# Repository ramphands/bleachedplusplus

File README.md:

# bleached++
slightly expanded and simplified version of the original Bleached PCB design by [andr-ew](https://github.com/andr-ew/bleached)

Bleached++ in operation

Render of the board

PCB layout with dimensions

## BOM
### board:
1x TeensyLC

2x 14-pin pin headers.

9x 10K linear potentiometers

### mounting HW:
4x 10mm M2.5 female-female standoffs - to be used between the board and the top panel

4x 5mm* M2.5 male-female standoffs  - to be used between the board and the bottom panel (*any length >3mm would be fine)

8x M2.5 5mm length screws

## PCBs

Gerbers are available as a .zip file in the GBR directory.  Simply provide the .zip file to a fabrication house.  JLCPCB is perhaps the most inexpensive.  If using JLCPCB, be sure to use the "specify a location" option to place the unsightly order code under the Teensy, as seen in the render.  The option looks like this:

## Firmware

Firmware has been modified from the original Bleached firmware to include the two additional potentiometers.

Also, an additional dual-bank firmware is available incorporating the changes made by [mat](https://github.com/justmat/) which allows for a dual 8-bank configuration.  The active bank is selectable with the lower-left potentiometer, with feedback provided by the Teensy LED.

## Top/bottom panels/enclosure

An SVG file is provided for making your own top/bottom panels.  Use Inkscape or other SVG-reading software to view the file.  All elements are seperated into individual layers, so you are able to hide/show the appropriate information.  In my case, I make only the outline and all the centrepunch marking crosses visible, then save as a PDF and print at a 1:1 size. I use this as a template for cutting and drilling a blank top panel.  I then hide the marking crosses for the LED and potentiometers, repeat the PDF process and use the resultant template for the bottom panel.

## NOTE

Design has been tested as of 16th Sept 2021 and works as intended with the firmware.

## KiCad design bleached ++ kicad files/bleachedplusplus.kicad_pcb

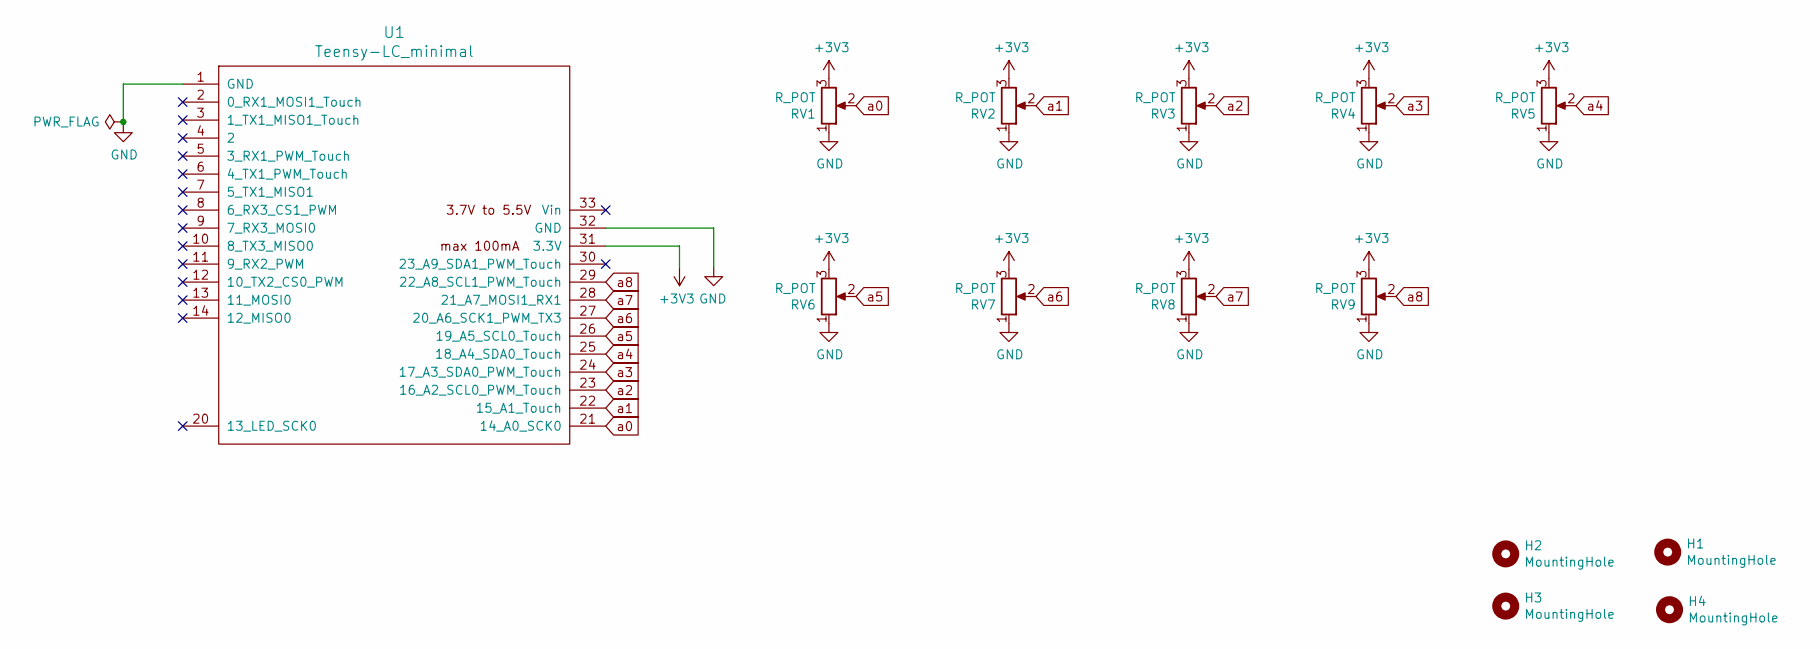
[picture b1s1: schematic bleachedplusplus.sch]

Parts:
H1, H2, H3, H4: MountingHole; MountingHole_2.7mm_M2.5_DIN965_Pad
RV1, RV2, RV3, RV4, RV5, RV6, RV7, RV8, RV9: R_POT; Potentiometer_Alpha_RD901F-40-00D_Single_Vertical
U1: Teensy-LC_minimal; Teensy_LC_minimal

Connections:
+3V3: RV1.3, RV2.3, RV3.3, RV4.3, RV5.3, RV6.3, RV7.3, RV8.3, RV9.3, U1.31 (3.3V)
GND: RV1.1, RV2.1, RV3.1, RV4.1, RV5.1, RV6.1, RV7.1, RV8.1, RV9.1, U1.1 (GND), U1.32 (GND)
a0: RV1.2, U1.21 (14_A0_SCK0)
a1: RV2.2, U1.22 (15_A1_Touch)
a2: RV3.2, U1.23 (16_A2_SCL0_PWM_Touch)
a3: RV4.2, U1.24 (17_A3_SDA0_PWM_Touch)
a4: RV5.2, U1.25 (18_A4_SDA0_Touch)
a5: RV6.2, U1.26 (19_A5_SCL0_Touch)
a6: RV7.2, U1.27 (20_A6_SCK1_PWM_TX3)
a7: RV8.2, U1.28 (21_A7_MOSI1_RX1)
a8: RV9.2, U1.29 (22_A8_SCL1_PWM_Touch)

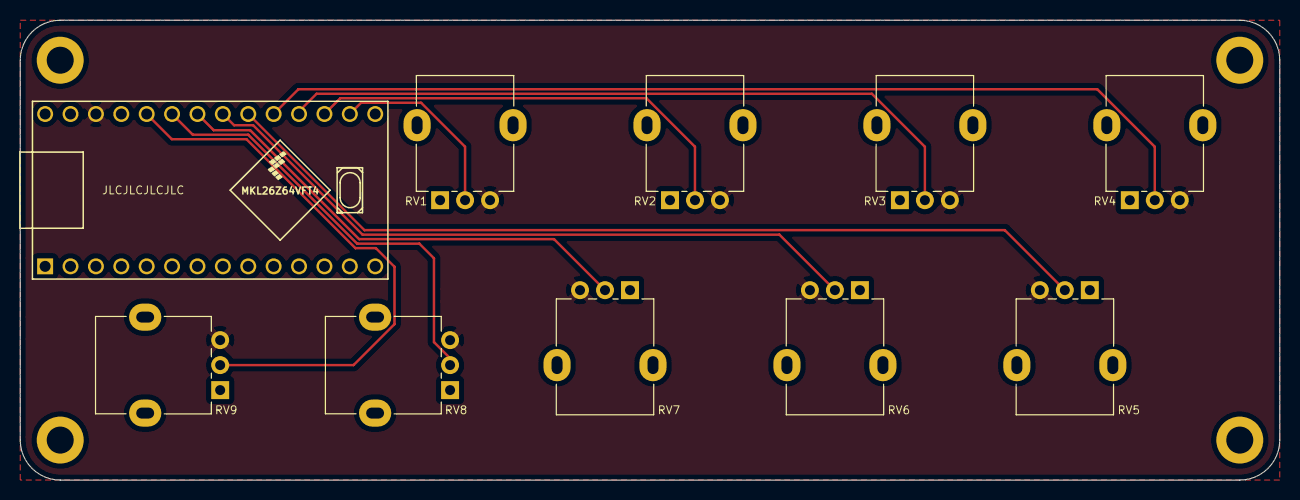
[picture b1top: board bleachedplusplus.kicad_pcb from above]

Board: 2 copper layers, 126.0 x 46.0 mm, 14 parts (0 on the bottom side), 11 nets.

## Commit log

2021-08-25 Add files via upload
    Contains SVG file for making your own case panels.
    Use the layer visibility options to select the relevant options ie hiding the LED/potentiometer drill holes when printing/exporting the "bottom" panel.
2021-08-31 Add files via upload
    fixed potentiometer rotation
